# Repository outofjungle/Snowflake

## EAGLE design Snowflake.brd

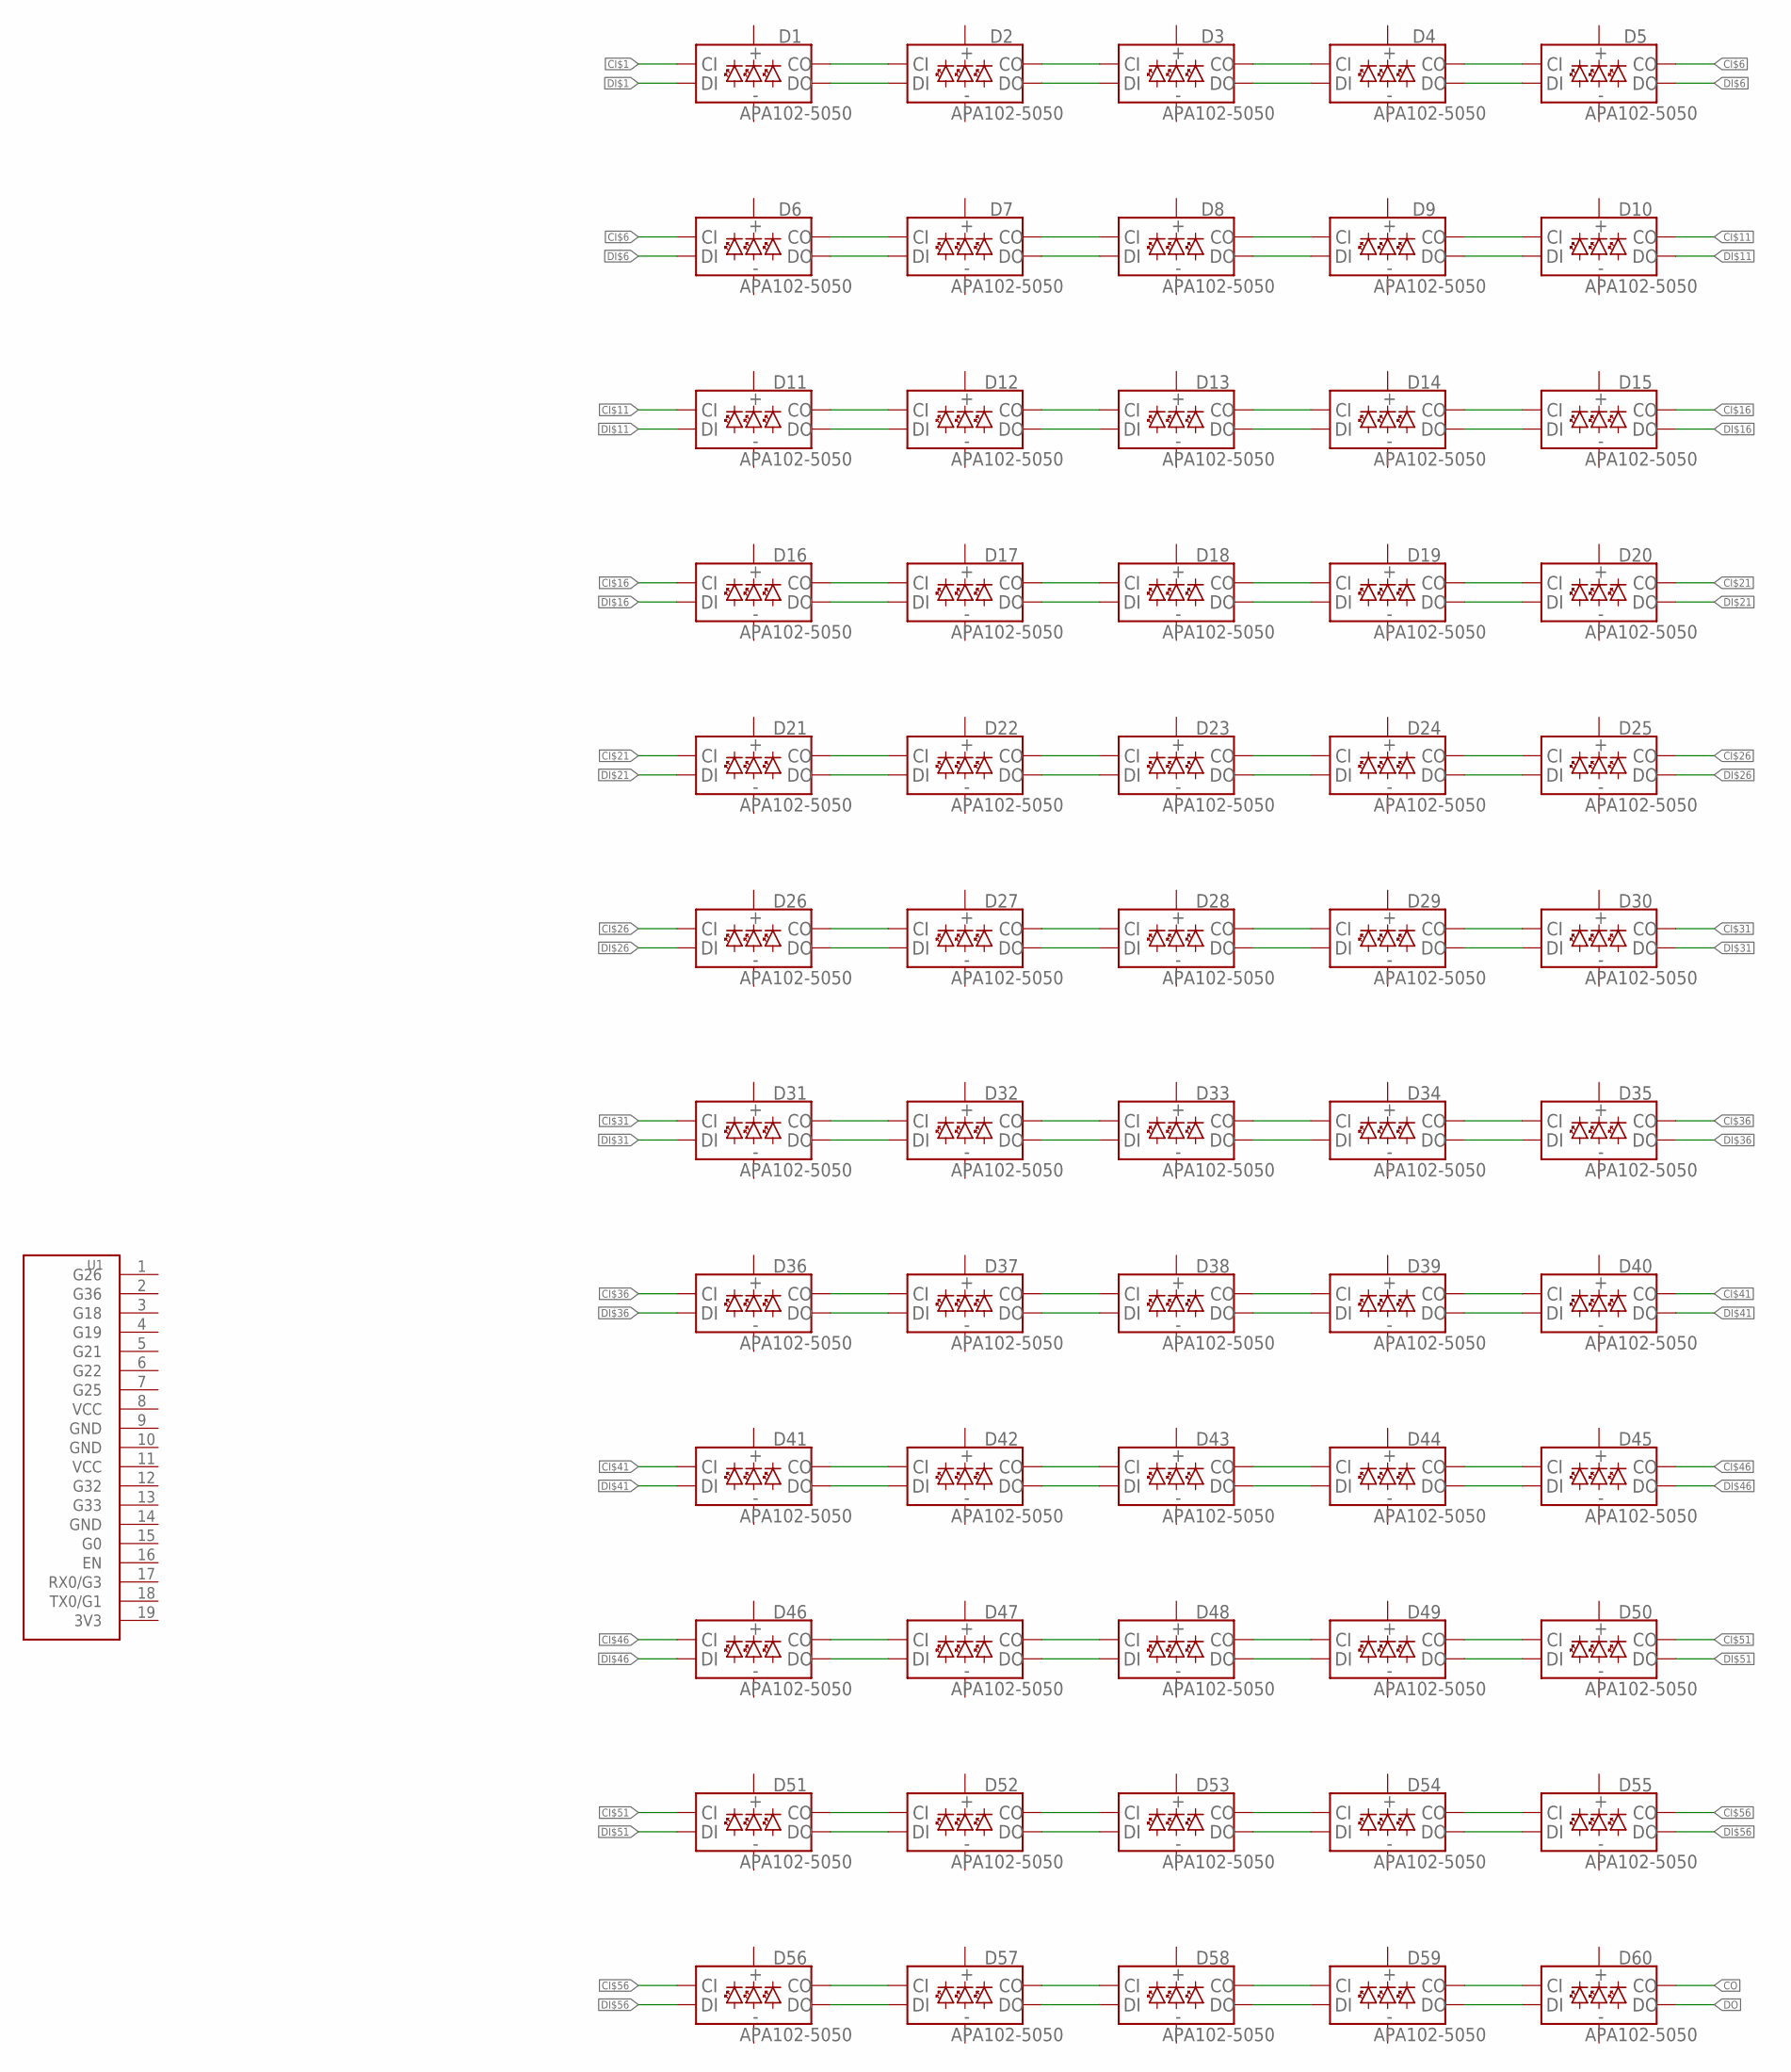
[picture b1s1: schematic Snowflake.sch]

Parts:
D1, D2, D3, D4, D5, D6, D7, D8, D9, D10, D11, D12, D13, D14, D15, D16, D17, D18, D19, D20, D21, D22, D23, D24, D25, D26, D27, D28, D29, D30, D31, D32, D33, D34, D35, D36, D37, D38, D39, D40, D41, D42, D43, D44, D45, D46, D47, D48, D49, D50, D51, D52, D53, D54, D55, D56, D57, D58, D59, D60: APA102-5050
U1: M5STAMP-PICO

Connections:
3V3: U1.19 (3V3)
CI$1: D1.P2 (CI)
CI$2: D1.P5 (CO), D2.P2 (CI)
CI$3: D2.P5 (CO), D3.P2 (CI)
CI$4: D3.P5 (CO), D4.P2 (CI)
CI$5: D4.P5 (CO), D5.P2 (CI)
CI$6: D5.P5 (CO), D6.P2 (CI)
CI$7: D6.P5 (CO), D7.P2 (CI)
CI$8: D7.P5 (CO), D8.P2 (CI)
CI$9: D8.P5 (CO), D9.P2 (CI)
CI$10: D9.P5 (CO), D10.P2 (CI)
CI$11: D10.P5 (CO), D11.P2 (CI)
CI$12: D11.P5 (CO), D12.P2 (CI)
CI$13: D12.P5 (CO), D13.P2 (CI)
CI$14: D13.P5 (CO), D14.P2 (CI)
CI$15: D14.P5 (CO), D15.P2 (CI)
CI$16: D15.P5 (CO), D16.P2 (CI)
CI$17: D16.P5 (CO), D17.P2 (CI)
CI$18: D17.P5 (CO), D18.P2 (CI)
CI$19: D18.P5 (CO), D19.P2 (CI)
CI$20: D19.P5 (CO), D20.P2 (CI)
CI$21: D20.P5 (CO), D21.P2 (CI)
CI$22: D21.P5 (CO), D22.P2 (CI)
CI$23: D22.P5 (CO), D23.P2 (CI)
CI$24: D23.P5 (CO), D24.P2 (CI)
CI$25: D24.P5 (CO), D25.P2 (CI)
CI$26: D25.P5 (CO), D26.P2 (CI)
CI$27: D26.P5 (CO), D27.P2 (CI)
CI$28: D27.P5 (CO), D28.P2 (CI)
CI$29: D28.P5 (CO), D29.P2 (CI)
CI$30: D29.P5 (CO), D30.P2 (CI)
CI$31: D30.P5 (CO), D31.P2 (CI)
CI$32: D31.P5 (CO), D32.P2 (CI)
CI$33: D32.P5 (CO), D33.P2 (CI)
CI$34: D33.P5 (CO), D34.P2 (CI)
CI$35: D34.P5 (CO), D35.P2 (CI)
CI$36: D35.P5 (CO), D36.P2 (CI)
CI$37: D36.P5 (CO), D37.P2 (CI)
CI$38: D37.P5 (CO), D38.P2 (CI)
CI$39: D38.P5 (CO), D39.P2 (CI)
CI$40: D39.P5 (CO), D40.P2 (CI)
CI$41: D40.P5 (CO), D41.P2 (CI)
CI$42: D41.P5 (CO), D42.P2 (CI)
CI$43: D42.P5 (CO), D43.P2 (CI)
CI$44: D43.P5 (CO), D44.P2 (CI)
CI$45: D44.P5 (CO), D45.P2 (CI)
CI$46: D45.P5 (CO), D46.P2 (CI)
CI$47: D46.P5 (CO), D47.P2 (CI)
CI$48: D47.P5 (CO), D48.P2 (CI)
CI$49: D48.P5 (CO), D49.P2 (CI)
CI$50: D49.P5 (CO), D50.P2 (CI)
CI$51: D50.P5 (CO), D51.P2 (CI)
CI$52: D51.P5 (CO), D52.P2 (CI)
CI$53: D52.P5 (CO), D53.P2 (CI)
CI$54: D53.P5 (CO), D54.P2 (CI)
CI$55: D54.P5 (CO), D55.P2 (CI)
CI$56: D55.P5 (CO), D56.P2 (CI)
CI$57: D56.P5 (CO), D57.P2 (CI)
CI$58: D57.P5 (CO), D58.P2 (CI)
CI$59: D58.P5 (CO), D59.P2 (CI)
CI$60: D59.P5 (CO), D60.P2 (CI)
CO: D60.P5 (CO)
DI$1: D1.P1 (DI)
DI$2: D1.P6 (DO), D2.P1 (DI)
DI$3: D2.P6 (DO), D3.P1 (DI)
DI$4: D3.P6 (DO), D4.P1 (DI)
DI$5: D4.P6 (DO), D5.P1 (DI)
DI$6: D5.P6 (DO), D6.P1 (DI)
DI$7: D6.P6 (DO), D7.P1 (DI)
DI$8: D7.P6 (DO), D8.P1 (DI)
DI$9: D8.P6 (DO), D9.P1 (DI)
DI$10: D9.P6 (DO), D10.P1 (DI)
DI$11: D10.P6 (DO), D11.P1 (DI)
DI$12: D11.P6 (DO), D12.P1 (DI)
DI$13: D12.P6 (DO), D13.P1 (DI)
DI$14: D13.P6 (DO), D14.P1 (DI)
DI$15: D14.P6 (DO), D15.P1 (DI)
DI$16: D15.P6 (DO), D16.P1 (DI)
DI$17: D16.P6 (DO), D17.P1 (DI)
DI$18: D17.P6 (DO), D18.P1 (DI)
DI$19: D18.P6 (DO), D19.P1 (DI)
DI$20: D19.P6 (DO), D20.P1 (DI)
DI$21: D20.P6 (DO), D21.P1 (DI)
DI$22: D21.P6 (DO), D22.P1 (DI)
DI$23: D22.P6 (DO), D23.P1 (DI)
DI$24: D23.P6 (DO), D24.P1 (DI)
DI$25: D24.P6 (DO), D25.P1 (DI)
DI$26: D25.P6 (DO), D26.P1 (DI)
DI$27: D26.P6 (DO), D27.P1 (DI)
DI$28: D27.P6 (DO), D28.P1 (DI)
DI$29: D28.P6 (DO), D29.P1 (DI)
DI$30: D29.P6 (DO), D30.P1 (DI)
DI$31: D30.P6 (DO), D31.P1 (DI)
DI$32: D31.P6 (DO), D32.P1 (DI)
DI$33: D32.P6 (DO), D33.P1 (DI)
DI$34: D33.P6 (DO), D34.P1 (DI)
DI$35: D34.P6 (DO), D35.P1 (DI)
DI$36: D35.P6 (DO), D36.P1 (DI)
DI$37: D36.P6 (DO), D37.P1 (DI)
DI$38: D37.P6 (DO), D38.P1 (DI)
DI$39: D38.P6 (DO), D39.P1 (DI)
DI$40: D39.P6 (DO), D40.P1 (DI)
DI$41: D40.P6 (DO), D41.P1 (DI)
DI$42: D41.P6 (DO), D42.P1 (DI)
DI$43: D42.P6 (DO), D43.P1 (DI)
DI$44: D43.P6 (DO), D44.P1 (DI)
DI$45: D44.P6 (DO), D45.P1 (DI)
DI$46: D45.P6 (DO), D46.P1 (DI)
DI$47: D46.P6 (DO), D47.P1 (DI)
DI$48: D47.P6 (DO), D48.P1 (DI)
DI$49: D48.P6 (DO), D49.P1 (DI)
DI$50: D49.P6 (DO), D50.P1 (DI)
DI$51: D50.P6 (DO), D51.P1 (DI)
DI$52: D51.P6 (DO), D52.P1 (DI)
DI$53: D52.P6 (DO), D53.P1 (DI)
DI$54: D53.P6 (DO), D54.P1 (DI)
DI$55: D54.P6 (DO), D55.P1 (DI)
DI$56: D55.P6 (DO), D56.P1 (DI)
DI$57: D56.P6 (DO), D57.P1 (DI)
DI$58: D57.P6 (DO), D58.P1 (DI)
DI$59: D58.P6 (DO), D59.P1 (DI)
DI$60: D59.P6 (DO), D60.P1 (DI)
DO: D60.P6 (DO)
GND: U1.9 (GND), U1.10 (GND), U1.14 (GND)
VCC: U1.8 (VCC), U1.11 (VCC)

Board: 2 copper layers, 61 parts (1 on the bottom side), 120 nets, no tracks yet.

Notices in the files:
parts and their libraries:
SparkFun-LED: Licensing: Creative Commons ShareAlike 4.0 International - https://creativecommons.org/licenses/by-sa/4.0
